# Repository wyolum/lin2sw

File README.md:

# lin2sw
small board to convert linear 3 pin regulator to switching regulator (TO220 compatible, eg 7805)

License
-------
[CERN Open Hardware Licence v1.2 ]

[CERN Open Hardware Licence v1.2 ]:http://www.ohwr.org/attachments/2388/cern_ohl_v_1_2.txt

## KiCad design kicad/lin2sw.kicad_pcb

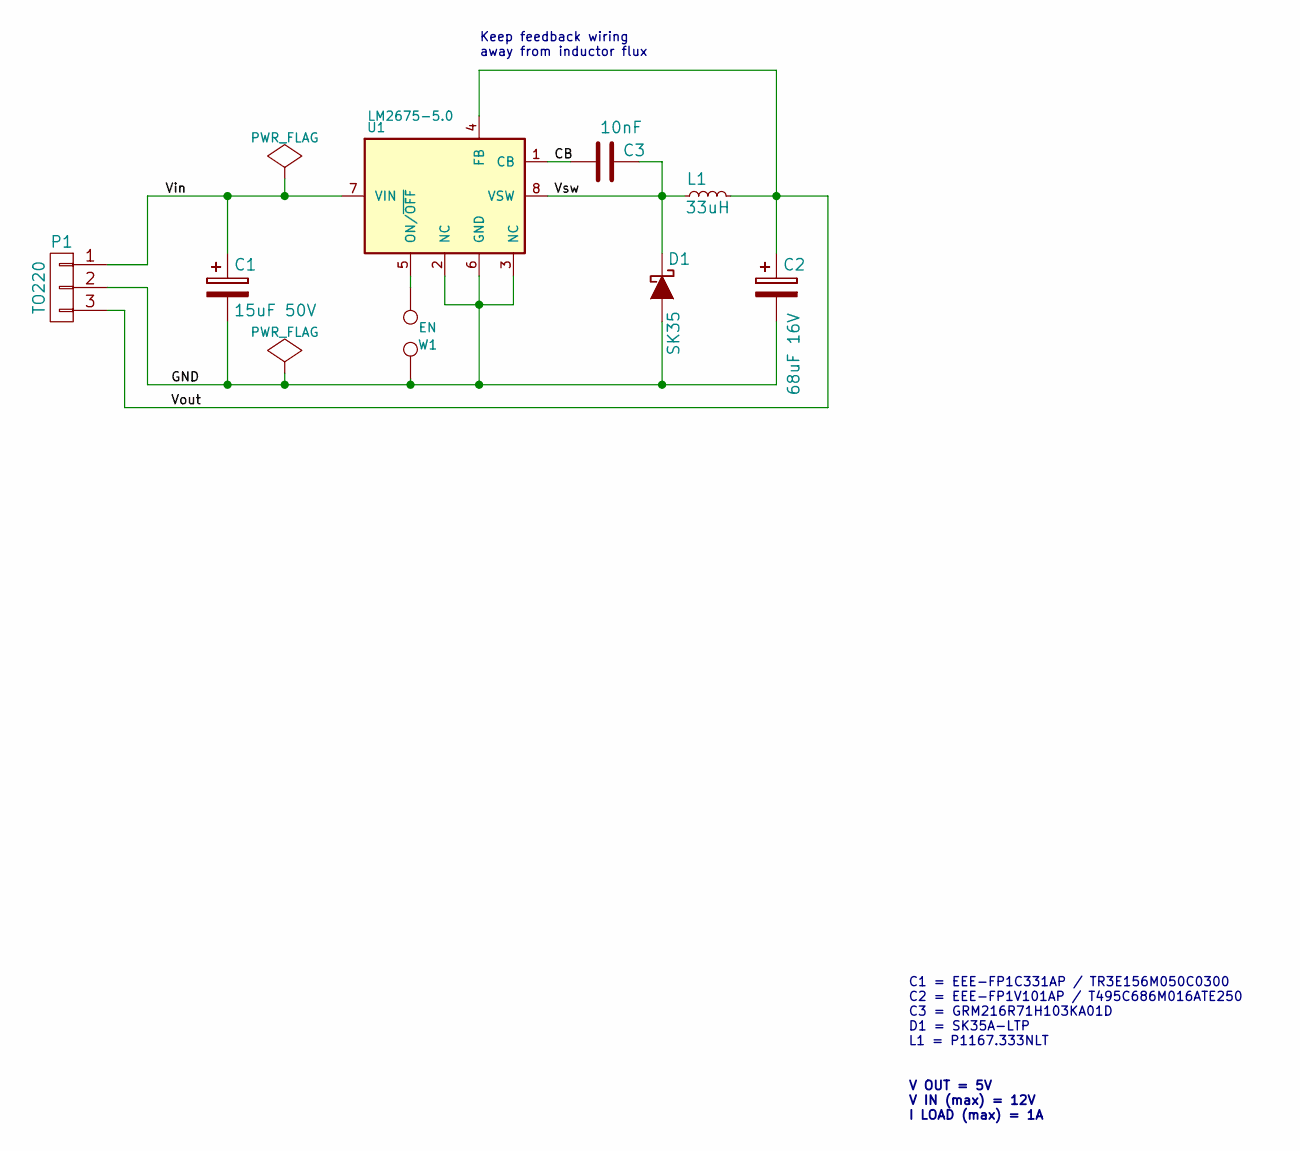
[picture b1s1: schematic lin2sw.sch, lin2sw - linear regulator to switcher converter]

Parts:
C1: 15uF 50V; C_2917_HandSoldering
C2: 68uF 16V; C_2312_HandSoldering
C3: 10nF; C_0805_HandSoldering
D1: SK35; Diode-SMA_Handsoldering
L1: 33uH; Choke_SMD_Pulse-PE1167
P1: TO220; Pin_Header_Straight_1x03
U1: LM2675-5.0; SO-8
W1: EN; R_0805_HandSoldering

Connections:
/CB: C3.2, U1.1 (CB)
/GND: C1.2, C2.2, D1.1 (A), P1.2, U1.2 (NC), U1.3 (NC), U1.6 (GND), W1.2
/Vin: C1.1, P1.1, U1.7 (VIN)
/Vout: C2.1, L1.2, P1.3, U1.4 (FB)
/Vsw: C3.1, D1.2 (K), L1.1, U1.8 (VSW)
unnamed: U1.5 (ON/~OFF), W1.1

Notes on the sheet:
Keep feedback wiring away from inductor flux
V OUT = 5V V IN (max) = 12V I LOAD (max) = 1A
C1 = EEE-FP1C331AP / TR3E156M050C0300 C2 = EEE-FP1V101AP / T495C686M016ATE250 C3 = GRM216R71H103KA01D D1 = SK35A-LTP L1 = P1167.333NLT

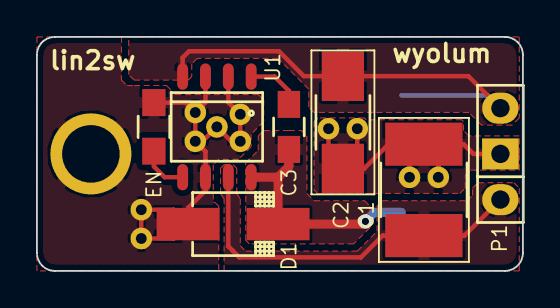
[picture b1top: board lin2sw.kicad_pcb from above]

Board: 2 copper layers, 27.0 x 13.0 mm, 8 parts (1 on the bottom side), 6 nets.

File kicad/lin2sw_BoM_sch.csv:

Reference, Value, Footprint, Datasheet
U1,LM2675-5.0,lin2sw:SO-8,
C1,15uF 50V,lin2sw:C_2917_HandSoldering,
C2,68uF 16V,lin2sw:C_2312_HandSoldering,
L1,33uH,lin2sw:Choke_SMD_Pulse-PE1167,
C3,10nF,lin2sw:C_0805_HandSoldering,
D1,SK35,lin2sw:Diode-SMA_Handsoldering,
P1,TO220,lin2sw:Pin_Header_Straight_1x03,
W1,EN,lin2sw:R_0805_HandSoldering,

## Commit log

2015-08-27 added gerbers
2015-08-28 minor mods to layout. Gerbers ready for fab
2015-09-23 added pictures of finished boards
